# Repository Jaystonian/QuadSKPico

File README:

# **README - QuadSKPico (Open-Source SID Emulation Hardware)**

## **About This Project**

QuadSKpico is an open-source hardware design for a **multi-RP2040-based SID chip emulator**. It is built from the ground up, independent of SIDKick, and aims to provide a **fully open alternative** for C64 audio enthusiasts.

## **Why This Project?**

- **Truly open-source**: Unlike other designs, all schematics and PCB layouts are **fully published**.
- **Expandable & Community-Driven**: Encourages modifications, improvements, and innovations.
- **No artificial restrictions**: Anyone can build, improve, and even sell hardware based on this design.

## **License & Usage**

- This hardware is licensed under the **CERN OHL-S 2.0**, ensuring it remains open and free.
- The firmware it runs is released under **GPLv3**, meaning modifications must also remain open-source.
- This project is **not affiliated with or derived from SIDKick hardware**, though it may run compatible software.

## **How to Contribute**

Pull requests, hardware modifications, and software contributions are welcome! Feel free to fork, improve, and share your work.

## **Credits**

- Hardware Designed by **JAYSTONIAN**
- Inspired by the open-source hardware movement and the SID emulation community.

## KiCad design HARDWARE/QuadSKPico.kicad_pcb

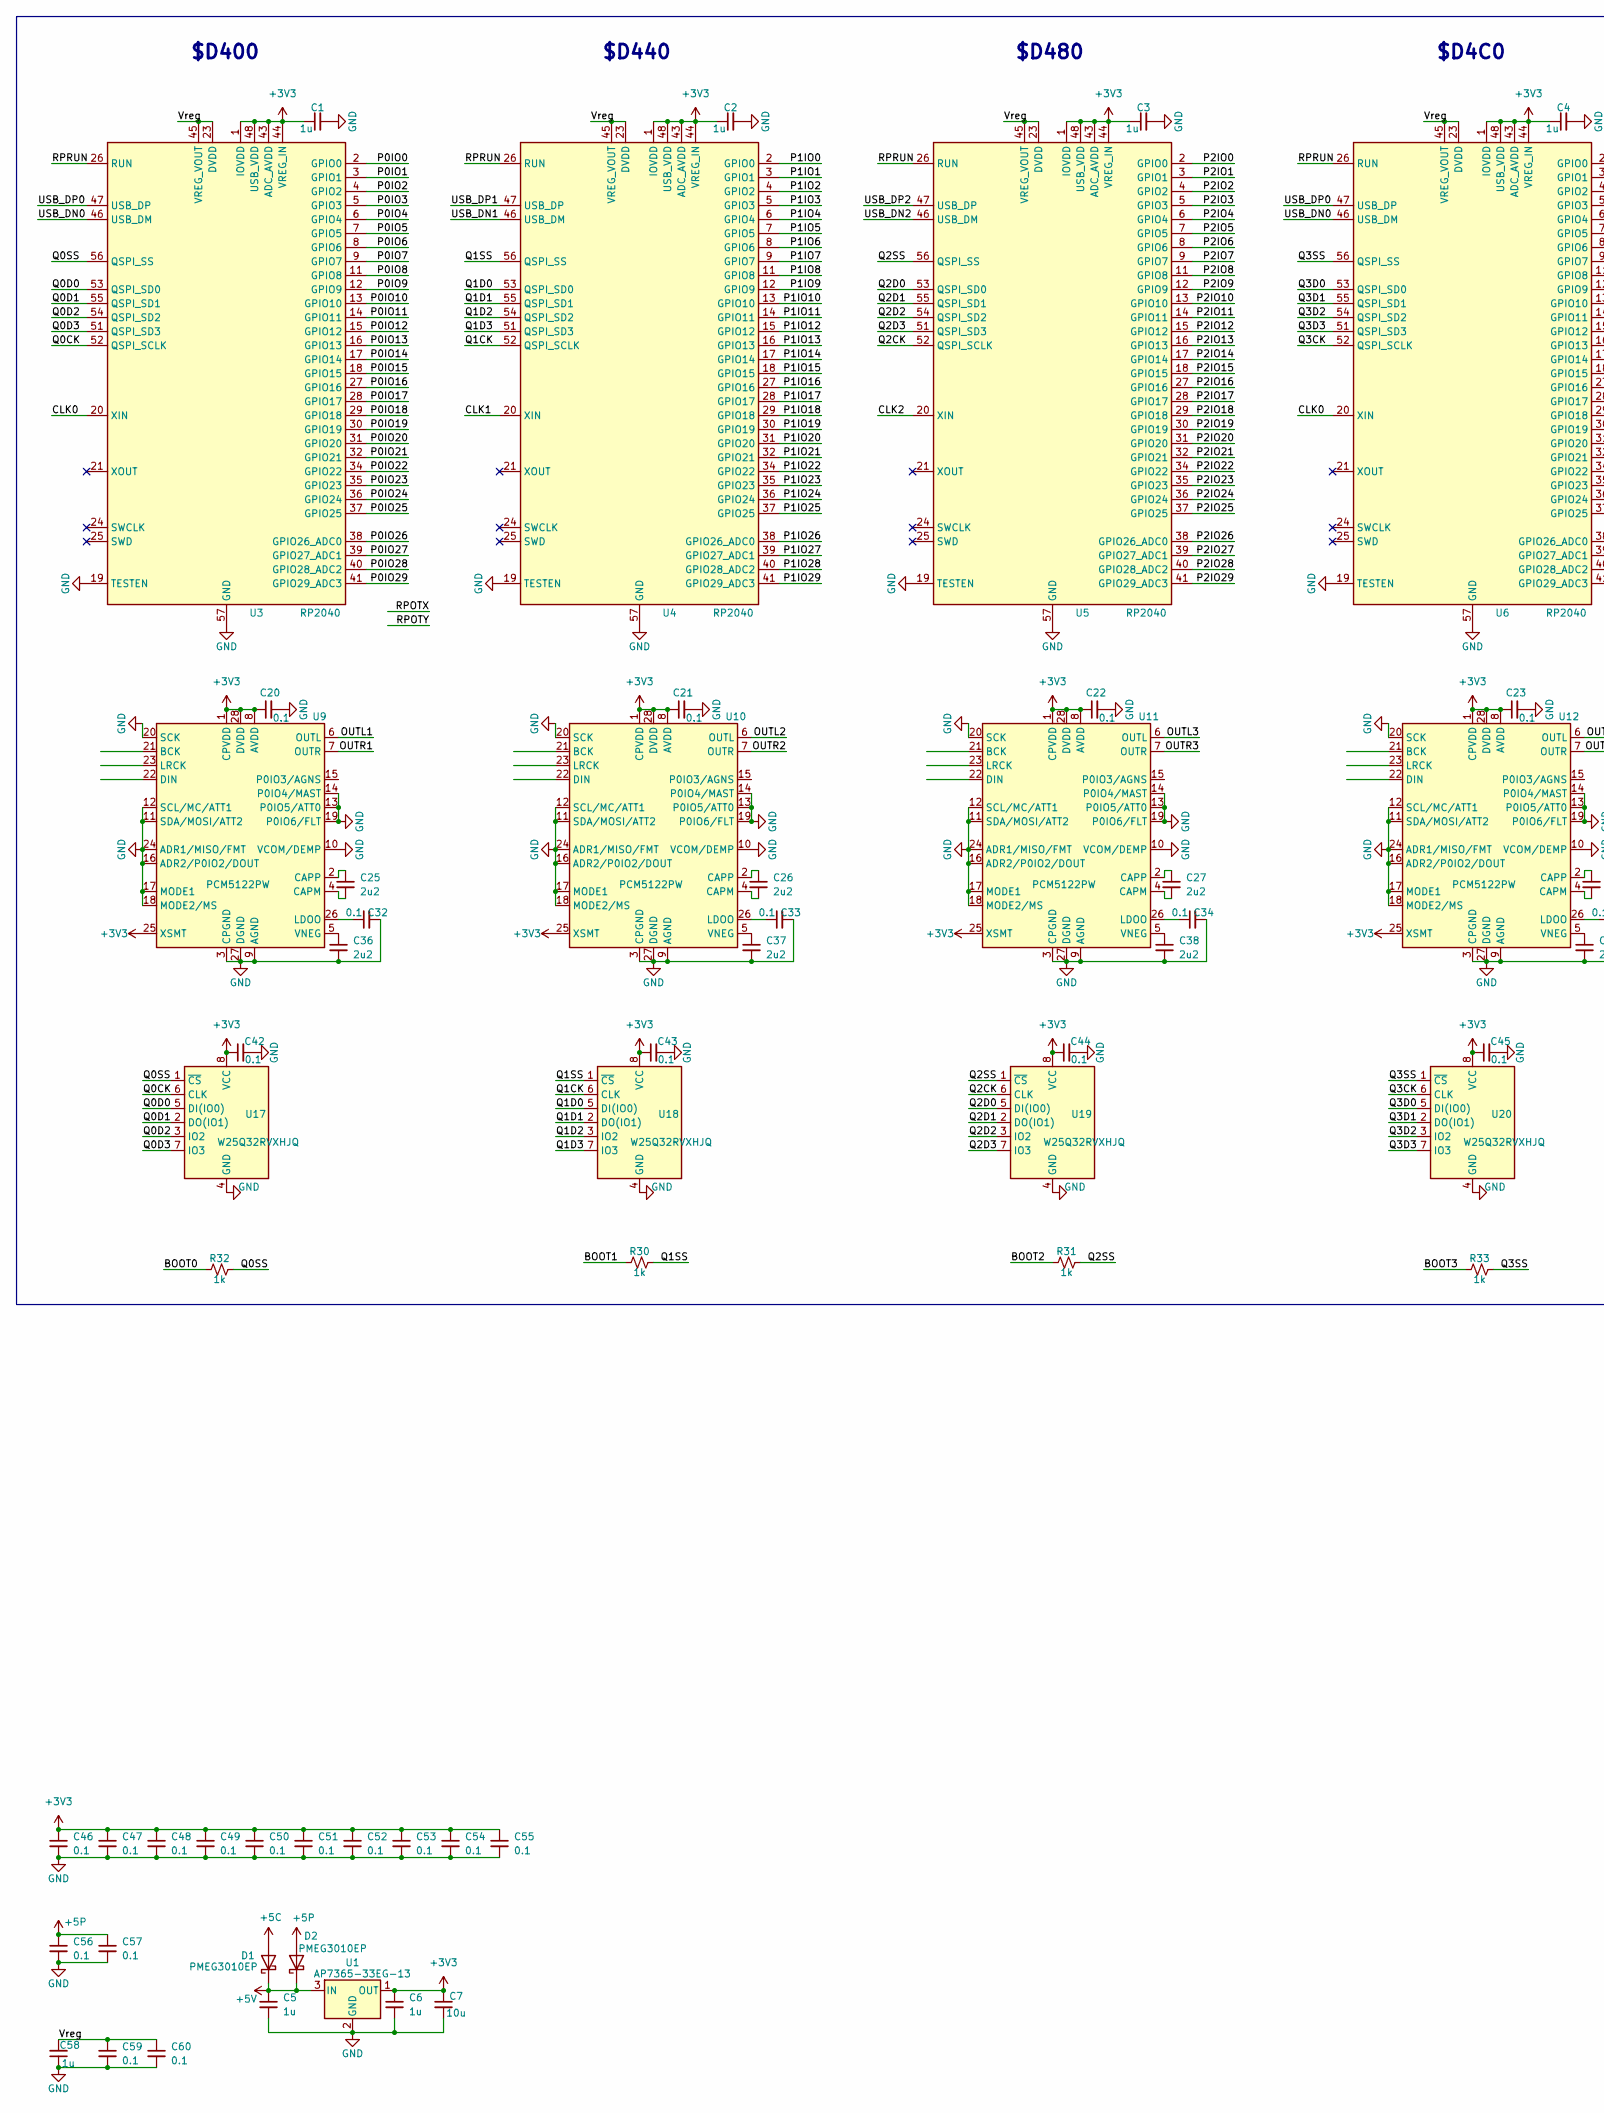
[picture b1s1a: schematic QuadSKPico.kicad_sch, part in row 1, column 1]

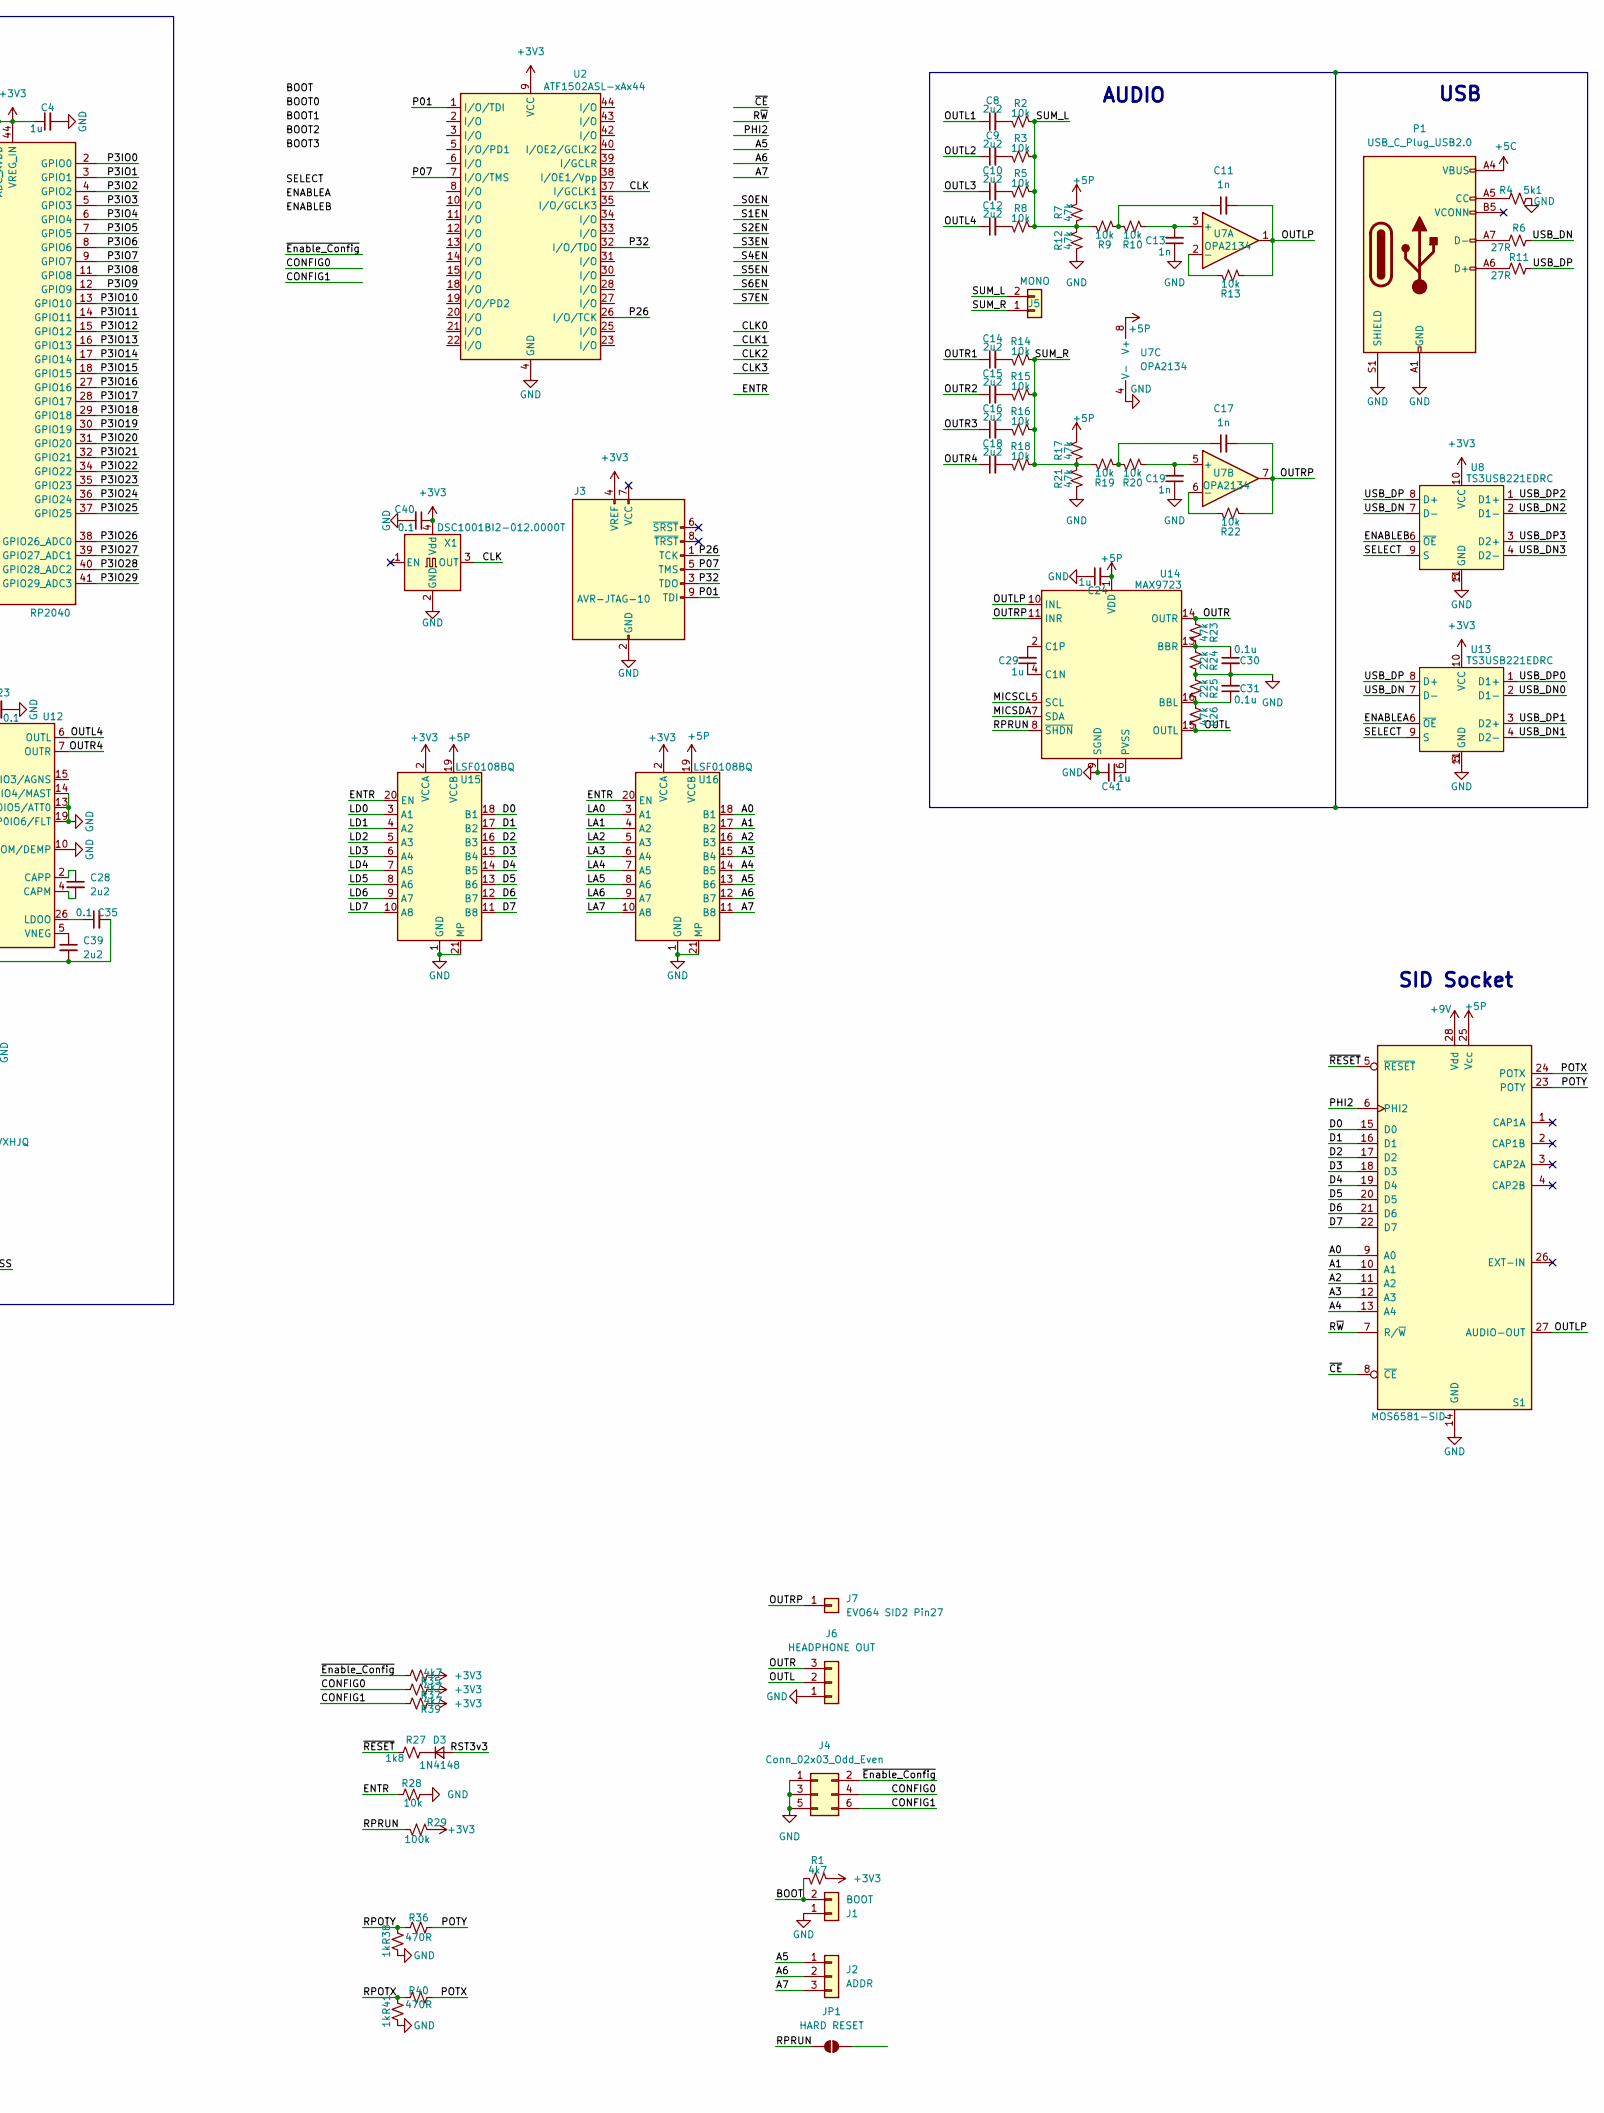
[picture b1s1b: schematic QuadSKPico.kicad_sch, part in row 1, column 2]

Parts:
C1, C2, C3, C4, C5, C6, C24, C29, C41, C58: 1u; C_0805_2012Metric_Pad1.18x1.45mm_HandSolder
C7: 10u; C_0805_2012Metric_Pad1.18x1.45mm_HandSolder
C8, C9, C10, C12, C14, C15, C16, C18, C25, C26, C27, C28, C36, C37, C38, C39: 2u2; C_0805_2012Metric_Pad1.18x1.45mm_HandSolder
C11, C13, C17, C19: 1n; C_0805_2012Metric_Pad1.18x1.45mm_HandSolder
C20, C21, C22, C23, C32, C33, C34, C35, C40, C42, C43, C44, C45, C46, C47, C48, C49, C50, C51, C52, C53, C54, C55, C56, C57, C59, C60: 0.1; C_0805_2012Metric_Pad1.18x1.45mm_HandSolder
C30, C31: 0.1u; C_0805_2012Metric_Pad1.18x1.45mm_HandSolder
D1, D2: PMEG3010EP; D_SMA_Handsoldering
D3: 1N4148; D_MiniMELF
J1: BOOT; PinHeader_1x02_P2.54mm_Vertical
J2: ADDR; PinHeader_1x03_P2.54mm_Vertical
J3: AVR-JTAG-10; PinHeader_2x05_P2.54mm_Vertical
J4: Conn_02x03_Odd_Even; PinHeader_2x03_P2.54mm_Vertical
J5: MONO; PinHeader_1x02_P2.54mm_Vertical
J6: HEADPHONE OUT; PinHeader_1x03_P2.54mm_Vertical
J7: EVO64 SID2 Pin27; PinHeader_1x01_P2.54mm_Vertical
JP1: HARD RESET; SolderJumper-2_P1.3mm_Open_RoundedPad1.0x1.5mm
P1: USB_C_Plug_USB2.0; USB_C_Receptacle_GCT_USB4110
R1, R35, R37, R39: 4k7; C_0805_2012Metric_Pad1.18x1.45mm_HandSolder
R2, R3, R5, R8, R9, R10, R13, R14, R15, R16, R18, R19, R20, R22, R28: 10k; C_0805_2012Metric_Pad1.18x1.45mm_HandSolder
R4: 5k1; C_0805_2012Metric_Pad1.18x1.45mm_HandSolder
R6, R11: 27R; C_0805_2012Metric_Pad1.18x1.45mm_HandSolder
R7, R12, R17, R21, R23, R26: 47k; C_0805_2012Metric_Pad1.18x1.45mm_HandSolder
R24, R25: 22k; C_0805_2012Metric_Pad1.18x1.45mm_HandSolder
R27: 1k8; C_0805_2012Metric_Pad1.18x1.45mm_HandSolder
R29: 100k; C_0805_2012Metric_Pad1.18x1.45mm_HandSolder
R30, R31, R32, R33, R38, R41: 1k; C_0805_2012Metric_Pad1.18x1.45mm_HandSolder
R36, R40: 470R; C_0805_2012Metric_Pad1.18x1.45mm_HandSolder
S1: MOS6581-SID; DIP-28_W15.24mm_Socket
U1: AP7365-33EG-13; SOT-223-3_TabPin2
U2: ATF1502ASL-xAx44; TQFP-44_10x10mm_P0.8mm
U3, U4, U5, U6: RP2040; QFN-56-1EP_7x7mm_P0.4mm_EP3.2x3.2mm
U7: OPA2134; SOIC-8_3.9x4.9mm_P1.27mm
U8, U13: TS3USB221EDRC; VSON-10-1EP_3x3mm_P0.5mm_EP1.65x2.4mm_ThermalVias
U9, U10, U11, U12: PCM5122PW; TSSOP-28_4.4x9.7mm_P0.65mm
U14: MAX9723; TQFN-16-1EP_4x4mm_P0.65mm_EP2.1x2.1mm_ThermalVias
U15, U16: LSF0108BQ; DHVQFN-20-1EP_2.5x4.5mm_P0.5mm_EP1x3mm
U17, U18, U19, U20: W25Q32RVXHJQ; Winbond_USON-8-1EP_3x2mm_P0.5mm_EP0.2x1.6mm
X1: DSC1001BI2-012.0000T; Oscillator_SMD_TXC_7C-4Pin_5.0x3.2mm

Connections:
+3V3: C1.1, C2.1, C3.1, C4.1, C6.1, C7.1, C20.1, C21.1, C22.1, C23.1, C40.1, C42.1, C43.1, C44.1, C45.1, C46.1, C47.1, C48.1, C49.1, C50.1, C51.1, C52.1, C53.1, C54.1, C55.1, J3.4 (VREF), R1.1, R29.1, R35.1, R37.1, R39.1, U1.1 (OUT), U2.9 (VCC), U2.17 (VCC), U2.29 (VCC), U2.41 (VCC), U3.1 (IOVDD), U3.10 (IOVDD), U3.22 (IOVDD), U3.33 (IOVDD), U3.42 (IOVDD), U3.43 (ADC_AVDD), U3.44 (VREG_IN), U3.48 (USB_VDD), U3.49 (IOVDD), U4.1 (IOVDD), U4.10 (IOVDD), U4.22 (IOVDD), U4.33 (IOVDD), U4.42 (IOVDD), U4.43 (ADC_AVDD), U4.44 (VREG_IN), U4.48 (USB_VDD), U4.49 (IOVDD), U5.1 (IOVDD), U5.10 (IOVDD), U5.22 (IOVDD), U5.33 (IOVDD), U5.42 (IOVDD), U5.43 (ADC_AVDD), U5.44 (VREG_IN), U5.48 (USB_VDD), U5.49 (IOVDD), U6.1 (IOVDD), U6.10 (IOVDD), U6.22 (IOVDD), U6.33 (IOVDD), U6.42 (IOVDD), U6.43 (ADC_AVDD), U6.44 (VREG_IN), U6.48 (USB_VDD), U6.49 (IOVDD), U8.10 (VCC), U9.1 (CPVDD), U9.8 (AVDD), U9.25 (XSMT), U9.28 (DVDD), U10.1 (CPVDD), U10.8 (AVDD), U10.25 (XSMT), U10.28 (DVDD), U11.1 (CPVDD), U11.8 (AVDD), U11.25 (XSMT), U11.28 (DVDD), U12.1 (CPVDD), U12.8 (AVDD), U12.25 (XSMT), U12.28 (DVDD), U13.10 (VCC), U15.2 (VCCA), U16.2 (VCCA), U17.8 (VCC), U18.8 (VCC), U19.8 (VCC), U20.8 (VCC), X1.4 (Vdd)
+5C: D1.2 (A), P1.A4 (VBUS), P1.A9 (VBUS), P1.B4 (VBUS), P1.B9 (VBUS)
+5P: C24.2, C56.1, C57.1, D2.2 (A), R7.1, R17.1, S1.25 (Vcc), U7.8 (V+), U14.1 (VDD), U15.19 (VCCB), U16.19 (VCCB)
+5V: C5.1, D1.1 (K), D2.1 (K), U1.3 (IN)
+9V: S1.28 (Vdd)
/A0: S1.9 (A0), U16.18 (B1)
/A1: S1.10 (A1), U16.17 (B2)
/A2: S1.11 (A2), U16.16 (B3)
/A3: S1.12 (A3), U16.15 (B4)
/A4: S1.13 (A4), U16.14 (B5)
/A5: J2.1, U16.13 (B6)
/A6: J2.2, U16.12 (B7)
/A7: J2.3, U16.11 (B8)
/BOOT: J1.2, R1.2
/BOOT0: R32.1
/BOOT1: R30.1
/BOOT2: R31.1
/BOOT3: R33.1
/CLK: U2.37 (I/GCLK1), X1.3 (OUT)
/CLK0: U3.20 (XIN), U6.20 (XIN)
/CLK1: U4.20 (XIN)
/CLK2: U5.20 (XIN)
/CONFIG0: J4.4, R37.2
/CONFIG1: J4.6, R39.2
/D0: S1.15 (D0), U15.18 (B1)
/D1: S1.16 (D1), U15.17 (B2)
/D2: S1.17 (D2), U15.16 (B3)
/D3: S1.18 (D3), U15.15 (B4)
/D4: S1.19 (D4), U15.14 (B5)
/D5: S1.20 (D5), U15.13 (B6)
/D6: S1.21 (D6), U15.12 (B7)
/D7: S1.22 (D7), U15.11 (B8)
/ENABLEA: U13.6 (~OE)
/ENABLEB: U8.6 (~OE)
/ENTR: R28.1, U15.20 (EN), U16.20 (EN)
/LA0: U16.3 (A1)
/LA1: U16.4 (A2)
/LA2: U16.5 (A3)
/LA3: U16.6 (A4)
/LA4: U16.7 (A5)
/LA5: U16.8 (A6)
/LA6: U16.9 (A7)
/LA7: U16.10 (A8)
/LD0: U15.3 (A1)
/LD1: U15.4 (A2)
/LD2: U15.5 (A3)
/LD3: U15.6 (A4)
/LD4: U15.7 (A5)
/LD5: U15.8 (A6)
/LD6: U15.9 (A7)
/LD7: U15.10 (A8)
/MICSCL: U14.5 (SCL)
/MICSDA: U14.7 (SDA)
/OUTL: J6.2, R26.2, U14.15 (OUTL)
/OUTL1: C8.1, U9.6 (OUTL)
/OUTL2: C9.1, U10.6 (OUTL)
/OUTL3: C10.1, U11.6 (OUTL)
/OUTL4: C12.1, U12.6 (OUTL)
/OUTLP: C11.2, R13.2, S1.27 (AUDIO-OUT), U7.1, U14.10 (INL)
/OUTR: J6.3, R23.1, U14.14 (OUTR)
/OUTR1: C14.1, U9.7 (OUTR)
/OUTR2: C15.1, U10.7 (OUTR)
/OUTR3: C16.1, U11.7 (OUTR)
/OUTR4: C18.1, U12.7 (OUTR)
/OUTRP: C17.2, J7.1, R22.2, U7.7, U14.11 (INR)
/P0IO0: U3.2 (GPIO0)
/P0IO1: U3.3 (GPIO1)
/P0IO2: U3.4 (GPIO2)
/P0IO3: U3.5 (GPIO3)
/P0IO4: U3.6 (GPIO4)
/P0IO5: U3.7 (GPIO5)
/P0IO6: U3.8 (GPIO6)
/P0IO7: U3.9 (GPIO7)
/P0IO8: U3.11 (GPIO8)
/P0IO9: U3.12 (GPIO9)
/P0IO10: U3.13 (GPIO10)
/P0IO11: U3.14 (GPIO11)
/P0IO12: U3.15 (GPIO12)
/P0IO13: U3.16 (GPIO13)
/P0IO14: U3.17 (GPIO14)
/P0IO15: U3.18 (GPIO15)
/P0IO16: U3.27 (GPIO16)
/P0IO17: U3.28 (GPIO17)
/P0IO18: U3.29 (GPIO18)
/P0IO19: U3.30 (GPIO19)
/P0IO20: U3.31 (GPIO20)
/P0IO21: U3.32 (GPIO21)
/P0IO22: U3.34 (GPIO22)
/P0IO23: U3.35 (GPIO23)
/P0IO24: U3.36 (GPIO24)
/P0IO25: U3.37 (GPIO25)
/P0IO26: U3.38 (GPIO26_ADC0)
/P0IO27: U3.39 (GPIO27_ADC1)
/P0IO28: U3.40 (GPIO28_ADC2)
/P0IO29: U3.41 (GPIO29_ADC3)
/P01: J3.9 (TDI), U2.1 (I/O/TDI)
/P1IO0: U4.2 (GPIO0)
/P1IO1: U4.3 (GPIO1)
/P1IO2: U4.4 (GPIO2)
/P1IO3: U4.5 (GPIO3)
/P1IO4: U4.6 (GPIO4)
/P1IO5: U4.7 (GPIO5)
/P1IO6: U4.8 (GPIO6)
/P1IO7: U4.9 (GPIO7)
/P1IO8: U4.11 (GPIO8)
/P1IO9: U4.12 (GPIO9)
/P1IO10: U4.13 (GPIO10)
/P1IO11: U4.14 (GPIO11)
/P1IO12: U4.15 (GPIO12)
/P1IO13: U4.16 (GPIO13)
/P1IO14: U4.17 (GPIO14)
/P1IO15: U4.18 (GPIO15)
/P1IO16: U4.27 (GPIO16)
/P1IO17: U4.28 (GPIO17)
/P1IO18: U4.29 (GPIO18)
/P1IO19: U4.30 (GPIO19)
/P1IO20: U4.31 (GPIO20)
/P1IO21: U4.32 (GPIO21)
/P1IO22: U4.34 (GPIO22)
/P1IO23: U4.35 (GPIO23)
/P1IO24: U4.36 (GPIO24)
/P1IO25: U4.37 (GPIO25)
/P1IO26: U4.38 (GPIO26_ADC0)
/P1IO27: U4.39 (GPIO27_ADC1)
/P1IO28: U4.40 (GPIO28_ADC2)
/P1IO29: U4.41 (GPIO29_ADC3)
/P2IO0: U5.2 (GPIO0)
/P2IO1: U5.3 (GPIO1)
/P2IO2: U5.4 (GPIO2)
/P2IO3: U5.5 (GPIO3)
/P2IO4: U5.6 (GPIO4)
/P2IO5: U5.7 (GPIO5)
/P2IO6: U5.8 (GPIO6)
/P2IO7: U5.9 (GPIO7)
/P2IO8: U5.11 (GPIO8)
/P2IO9: U5.12 (GPIO9)
/P2IO10: U5.13 (GPIO10)
/P2IO11: U5.14 (GPIO11)
/P2IO12: U5.15 (GPIO12)
/P2IO13: U5.16 (GPIO13)
/P2IO14: U5.17 (GPIO14)
/P2IO15: U5.18 (GPIO15)
/P2IO16: U5.27 (GPIO16)
/P2IO17: U5.28 (GPIO17)
/P2IO18: U5.29 (GPIO18)
/P2IO19: U5.30 (GPIO19)
/P2IO20: U5.31 (GPIO20)
/P2IO21: U5.32 (GPIO21)
/P2IO22: U5.34 (GPIO22)
/P2IO23: U5.35 (GPIO23)
/P2IO24: U5.36 (GPIO24)
/P2IO25: U5.37 (GPIO25)
/P2IO26: U5.38 (GPIO26_ADC0)
/P2IO27: U5.39 (GPIO27_ADC1)
/P2IO28: U5.40 (GPIO28_ADC2)
/P2IO29: U5.41 (GPIO29_ADC3)
/P3IO0: U6.2 (GPIO0)
/P3IO1: U6.3 (GPIO1)
/P3IO2: U6.4 (GPIO2)
/P3IO3: U6.5 (GPIO3)
/P3IO4: U6.6 (GPIO4)
/P3IO5: U6.7 (GPIO5)
/P3IO6: U6.8 (GPIO6)
/P3IO7: U6.9 (GPIO7)
/P3IO8: U6.11 (GPIO8)
/P3IO9: U6.12 (GPIO9)
/P3IO10: U6.13 (GPIO10)
/P3IO11: U6.14 (GPIO11)
/P3IO12: U6.15 (GPIO12)
/P3IO13: U6.16 (GPIO13)
/P3IO14: U6.17 (GPIO14)
/P3IO15: U6.18 (GPIO15)
/P3IO16: U6.27 (GPIO16)
/P3IO17: U6.28 (GPIO17)
/P3IO18: U6.29 (GPIO18)
/P3IO19: U6.30 (GPIO19)
/P3IO20: U6.31 (GPIO20)
/P3IO21: U6.32 (GPIO21)
/P3IO22: U6.34 (GPIO22)
/P3IO23: U6.35 (GPIO23)
/P3IO24: U6.36 (GPIO24)
/P3IO25: U6.37 (GPIO25)
/P3IO26: U6.38 (GPIO26_ADC0)
/P3IO27: U6.39 (GPIO27_ADC1)
/P3IO28: U6.40 (GPIO28_ADC2)
/P3IO29: U6.41 (GPIO29_ADC3)
/P07: J3.5 (TMS), U2.7 (I/O/TMS)
/P26: J3.1 (TCK), U2.26 (I/O/TCK)
/P32: J3.3 (TDO), U2.32 (I/O/TDO)
/PHI2: S1.6 (PHI2)
/POTX: R40.2, S1.24 (POTX)
/POTY: R36.2, S1.23 (POTY)
/Q0CK: U3.52 (QSPI_SCLK), U17.6 (CLK)
/Q0D0: U3.53 (QSPI_SD0), U17.5 (DI(IO0))
/Q0D1: U3.55 (QSPI_SD1), U17.2 (DO(IO1))
/Q0D2: U3.54 (QSPI_SD2), U17.3 (IO2)
/Q0D3: U3.51 (QSPI_SD3), U17.7 (IO3)
/Q0SS: R32.2, U3.56 (QSPI_SS), U17.1 (~CS)
/Q1CK: U4.52 (QSPI_SCLK), U18.6 (CLK)
/Q1D0: U4.53 (QSPI_SD0), U18.5 (DI(IO0))
/Q1D1: U4.55 (QSPI_SD1), U18.2 (DO(IO1))
/Q1D2: U4.54 (QSPI_SD2), U18.3 (IO2)
/Q1D3: U4.51 (QSPI_SD3), U18.7 (IO3)
/Q1SS: R30.2, U4.56 (QSPI_SS), U18.1 (~CS)
/Q2CK: U5.52 (QSPI_SCLK), U19.6 (CLK)
/Q2D0: U5.53 (QSPI_SD0), U19.5 (DI(IO0))
/Q2D1: U5.55 (QSPI_SD1), U19.2 (DO(IO1))
/Q2D2: U5.54 (QSPI_SD2), U19.3 (IO2)
/Q2D3: U5.51 (QSPI_SD3), U19.7 (IO3)
/Q2SS: R31.2, U5.56 (QSPI_SS), U19.1 (~CS)
/Q3CK: U6.52 (QSPI_SCLK), U20.6 (CLK)
/Q3D0: U6.53 (QSPI_SD0), U20.5 (DI(IO0))
/Q3D1: U6.55 (QSPI_SD1), U20.2 (DO(IO1))
/Q3D2: U6.54 (QSPI_SD2), U20.3 (IO2)
/Q3D3: U6.51 (QSPI_SD3), U20.7 (IO3)
/Q3SS: R33.2, U6.56 (QSPI_SS), U20.1 (~CS)
/RPOTX: R40.1, R41.2
/RPOTY: R36.1, R38.2
/RPRUN: JP1.1 (A), R29.2, U3.26 (RUN), U4.26 (RUN), U5.26 (RUN), U6.26 (RUN), U14.8 (~SHDN)
/RST3v3: D3.2 (A)
/R~W: S1.7 (R/~W)
/SELECT: U8.9 (S), U13.9 (S)
/SUM_L: J5.2, R2.1, R3.1, R5.1, R7.2, R8.1, R9.1, R12.1
/SUM_R: J5.1, R14.1, R15.1, R16.1, R17.2, R18.1, R19.1, R21.1
/USB_DN: R6.2, U8.7 (D-), U13.7 (D-)
/USB_DN0: U3.46 (USB_DM), U6.46 (USB_DM), U13.2 (D1-)
/USB_DN1: U4.46 (USB_DM), U13.4 (D2-)
/USB_DN2: U5.46 (USB_DM), U8.2 (D1-)
/USB_DN3: U8.4 (D2-)
/USB_DP: R11.2, U8.8 (D+), U13.8 (D+)
/USB_DP0: U3.47 (USB_DP), U6.47 (USB_DP), U13.1 (D1+)
/USB_DP1: U4.47 (USB_DP), U13.3 (D2+)
/USB_DP2: U5.47 (USB_DP), U8.1 (D1+)
/USB_DP3: U8.3 (D2+)
/Vreg: C58.2, C59.1, C60.1, U3.23 (DVDD), U3.45 (VREG_VOUT), U3.50 (DVDD), U4.23 (DVDD), U4.45 (VREG_VOUT), U4.50 (DVDD), U5.23 (DVDD), U5.45 (VREG_VOUT), U5.50 (DVDD), U6.23 (DVDD), U6.45 (VREG_VOUT), U6.50 (DVDD)
/~CE: S1.8 (~CE)
/~Enable_Config: J4.2, R35.2
/~RESET: R27.1, S1.5 (~RESET)
GND: C1.2, C2.2, C3.2, C4.2, C5.2, C6.2, C7.2, C13.1, C19.1, C20.2, C21.2, C22.2, C23.2, C24.1, C30.2, C31.2, C32.2, C33.2, C34.2, C35.2, C36.2, C37.2, C38.2, C39.2, C40.2, C41.2, C42.2, C43.2, C44.2, C45.2, C46.2, C47.2, C48.2, C49.2, C50.2, C51.2, C52.2, C53.2, C54.2, C55.2, C56.2, C57.2, C58.1, C59.2, C60.2, J1.1, J3.2 (GND), J3.10 (GND), J4.1, J4.3, J4.5, J6.1, P1.A1 (GND), P1.A12 (GND), P1.B1 (GND), P1.B12 (GND), P1.S1 (SHIELD), R4.2, R12.2, R21.2, R24.2, R25.1, R28.2, R38.1, R41.1, S1.14 (GND), U1.2 (GND), U2.4 (GND), U2.16 (GND), U2.24 (GND), U2.36 (GND), U3.19 (TESTEN), U3.57 (GND), U4.19 (TESTEN), U4.57 (GND), U5.19 (TESTEN), U5.57 (GND), U6.19 (TESTEN), U6.57 (GND), U7.4 (V-), U8.5 (GND), U8.11 (GND), U9.3 (CPGND), U9.9 (AGND), U9.10 (VCOM/DEMP), U9.11 (SDA/MOSI/ATT2), U9.12 (SCL/MC/ATT1), U9.13 (P0IO5/ATT0), U9.14 (P0IO4/MAST), U9.16 (ADR2/P0IO2/DOUT), U9.17 (MODE1), U9.18 (MODE2/MS), U9.19 (P0IO6/FLT), U9.20 (SCK), U9.24 (ADR1/MISO/FMT), U9.27 (DGND), U10.3 (CPGND), U10.9 (AGND), U10.10 (VCOM/DEMP), U10.11 (SDA/MOSI/ATT2), U10.12 (SCL/MC/ATT1), U10.13 (P0IO5/ATT0), U10.14 (P0IO4/MAST), U10.16 (ADR2/P0IO2/DOUT), U10.17 (MODE1), U10.18 (MODE2/MS), U10.19 (P0IO6/FLT), U10.20 (SCK), U10.24 (ADR1/MISO/FMT), U10.27 (DGND), U11.3 (CPGND), U11.9 (AGND), U11.10 (VCOM/DEMP), U11.11 (SDA/MOSI/ATT2), U11.12 (SCL/MC/ATT1), U11.13 (P0IO5/ATT0), U11.14 (P0IO4/MAST), U11.16 (ADR2/P0IO2/DOUT), U11.17 (MODE1), U11.18 (MODE2/MS), U11.19 (P0IO6/FLT), U11.20 (SCK), U11.24 (ADR1/MISO/FMT), U11.27 (DGND), U12.3 (CPGND), U12.9 (AGND), U12.10 (VCOM/DEMP), U12.11 (SDA/MOSI/ATT2), U12.12 (SCL/MC/ATT1), U12.13 (P0IO5/ATT0), U12.14 (P0IO4/MAST), U12.16 (ADR2/P0IO2/DOUT), U12.17 (MODE1), U12.18 (MODE2/MS), U12.19 (P0IO6/FLT), U12.20 (SCK), U12.24 (ADR1/MISO/FMT), U12.27 (DGND), U13.5 (GND), U13.11 (GND), U14.3 (PGND), U14.9 (SGND), U14.EP, U15.1 (GND), U15.21 (MP), U16.1 (GND), U16.21 (MP), U17.4 (GND), U18.4 (GND), U19.4 (GND), U20.4 (GND), X1.2 (GND)
unnamed: C8.2, R2.2
unnamed: C9.2, R3.2
unnamed: C10.2, R5.2
unnamed: C11.1, R9.2, R10.1
unnamed: C12.2, R8.2
unnamed: C14.2, R14.2
unnamed: C15.2, R15.2
unnamed: C16.2, R16.2
unnamed: C17.1, R19.2, R20.1
unnamed: C18.2, R18.2
unnamed: D3.1 (K), R27.2
unnamed: P1.A5 (CC), R4.1
unnamed: P1.A6 (D+), R11.1
unnamed: P1.A7 (D-), R6.1
unnamed: C13.2, R10.2, U7.3 (+)
unnamed: R13.1, U7.2 (-)
unnamed: C19.2, R20.2, U7.5 (+)
unnamed: R22.1, U7.6 (-)
unnamed: C25.2, U9.4 (CAPM)
unnamed: C25.1, U9.2 (CAPP)
unnamed: C32.1, U9.26 (LDOO)
unnamed: C36.1, U9.5 (VNEG)
unnamed: C26.2, U10.4 (CAPM)
unnamed: C26.1, U10.2 (CAPP)
unnamed: C33.1, U10.26 (LDOO)
unnamed: C37.1, U10.5 (VNEG)
unnamed: C27.2, U11.4 (CAPM)
unnamed: C27.1, U11.2 (CAPP)
unnamed: C34.1, U11.26 (LDOO)
unnamed: C38.1, U11.5 (VNEG)
unnamed: C28.2, U12.4 (CAPM)
unnamed: C28.1, U12.2 (CAPP)
unnamed: C35.1, U12.26 (LDOO)
unnamed: C39.1, U12.5 (VNEG)
unnamed: C31.1, R25.2, R26.1, U14.16 (BBL)
unnamed: C30.1, R23.2, R24.1, U14.13 (BBR)
unnamed: C29.1, U14.4 (C1N)
unnamed: C29.2, U14.2 (C1P)
SVSS: C41.1, U14.6 (PVSS), U14.12 (SVSS)

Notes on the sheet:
$D440
$D400
$D4C0
$D480
SID Socket
AUDIO
USB

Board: 2 copper layers, 134 parts (4 on the bottom side), 125 nets, no tracks yet.

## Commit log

2025-03-24 Update LICENSE
